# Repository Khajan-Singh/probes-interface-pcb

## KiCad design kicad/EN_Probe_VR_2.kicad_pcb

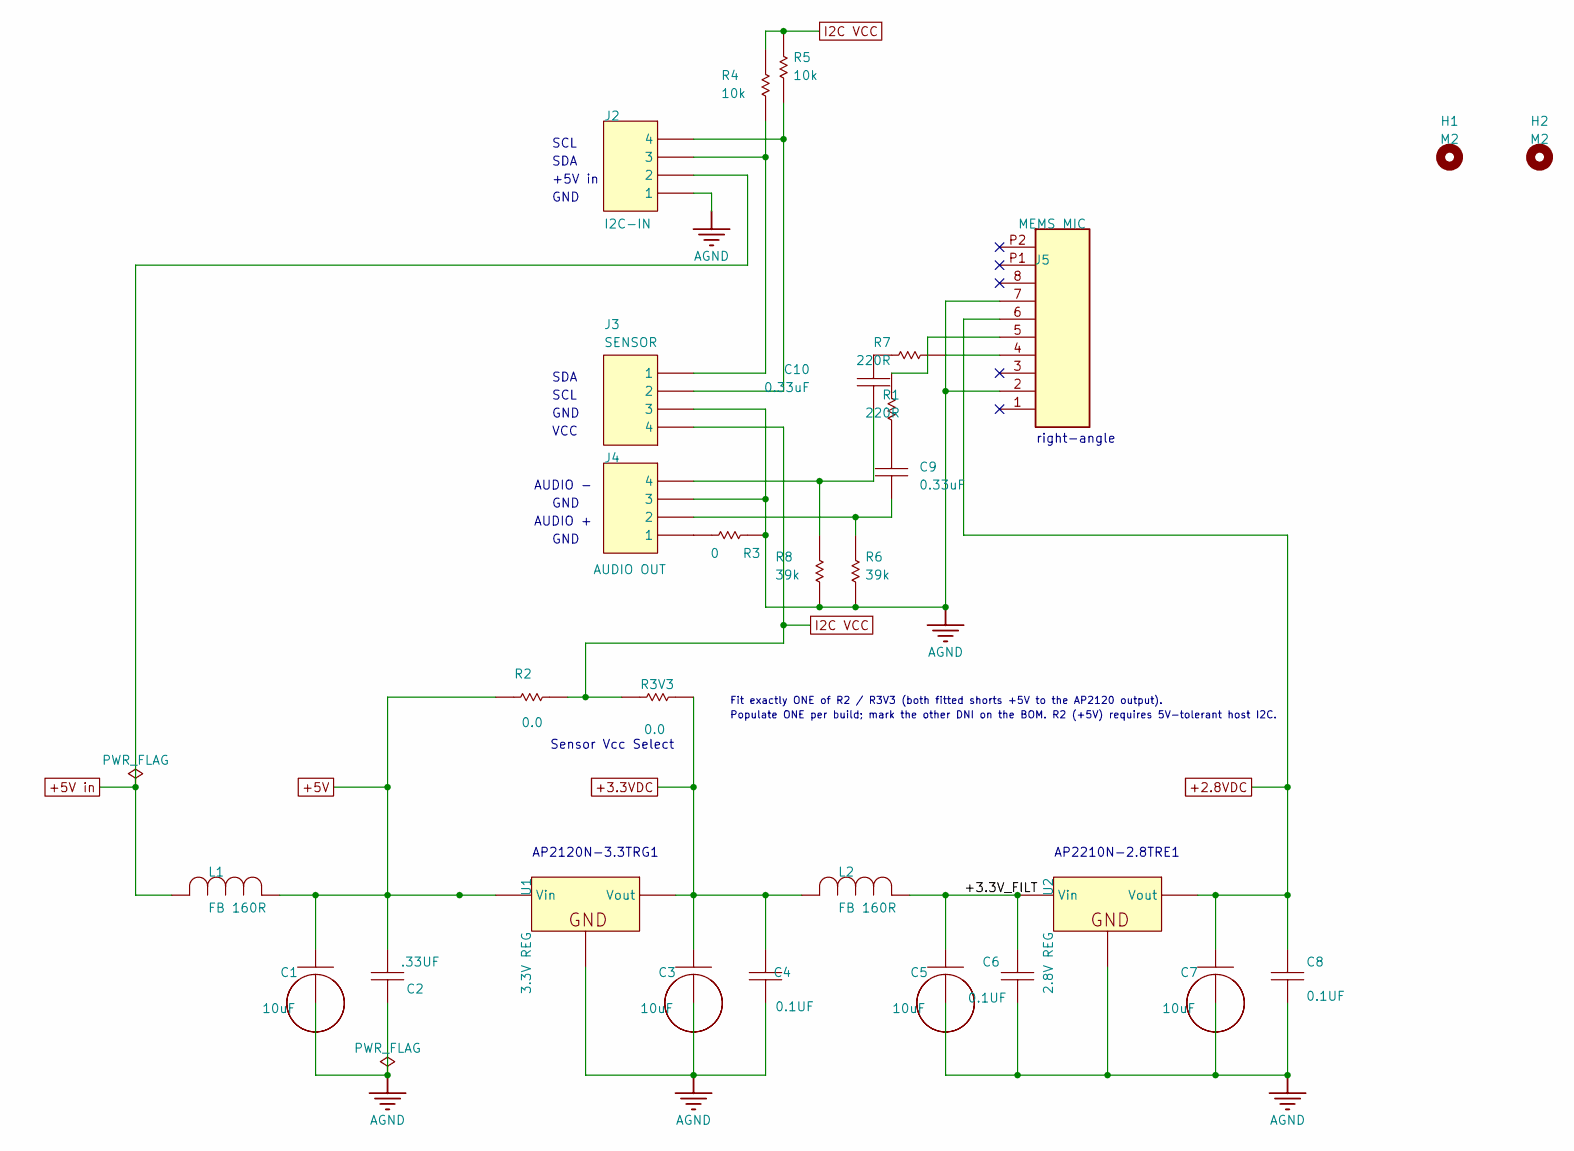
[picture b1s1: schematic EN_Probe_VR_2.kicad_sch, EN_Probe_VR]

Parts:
C1, C3, C5, C7: 10uF; C_0805_2012Metric; MANUFACTURER PART NUMBE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 GRM21BR61E106MA73L
C2: .33UF; C_0805_2012Metric; MANUFACTURER PN CL21B334KAFNNNG
C4, C6, C8: 0.1UF; C_0603_1608Metric; PART FIELD 1 0
C9: 0.33uF; C_0805_2012Metric; MANUFACTURER PN CL21B334KAFNNNG
C10: 0.33uF; C_0805_2012Metric
H1, H2: M2; MountingHole_2.2mm_M2
J2: I2C-IN; PinHeader_1x04_P2.54mm_Vertical; MANUFACTURER PN 640454-4
J3: SENSOR; PinHeader_1x04_P2.54mm_Vertical; MANUFACTURER PN 640454-4
J4: AUDIO OUT; PinHeader_1x04_P2.54mm_Vertical; MANUFACTURER PN 640454-4
J5: MEMS MIC; CON_527450897; MANUFACTURER_PART_NUMBER 527450897
L1, L2: FB 160R; 1206; MANUFACTURER_PART_NUMBER HI1206T161R-10
R1: 220R; R_0805_2012Metric; TOLERANCE_% 5
R2, R3, R3V3: 0R; R_0805_2012Metric; TOLERANCE_% 5
R4, R5: 10k; R_0805_2012Metric
R6, R8: 39k; R_0805_2012Metric
R7: 220R; R_0805_2012Metric
U1: 3.3V REG; SOT23-3; MANUFACTURER PART NUMBE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 AP2120N-3.3TRG1
U2: 2.8V REG; SOT23-3; MANUFACTURER PART NUMBE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 AP2210N-2.8TRE1

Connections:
+2.8VDC: C7.1, C8.2, J5.6, U2.2 (Vout)
+3.3VDC: C3.1, C4.1, L2.2, R3V3.2, U1.2 (Vout)
+5V: C1.1, C2.2, L1.1, R2.2, U1.3 (Vin)
+5V in: J2.2, L1.2
/+3.3V_FILT: C5.1, C6.2, L2.1, U2.3 (Vin)
AGND: C1.2, C2.1, C3.2, C4.2, C5.2, C6.1, C7.2, C8.1, J2.1, J3.3, J4.3, J5.2, J5.7, R3.1, R6.2, R8.2, U1.1 (GND), U2.1 (GND)
I2C VCC: J3.4, R2.1, R3V3.1, R4.1, R5.1
unnamed: C9.1, J4.2, R6.1
unnamed: C9.2, R1.2
unnamed: C10.1, R7.1
unnamed: C10.2, J4.4, R8.1
unnamed: J2.3, J3.1, R4.2
unnamed: J2.4, J3.2, R5.2
unnamed: J4.1, R3.2
unnamed: J5.4, R7.2
unnamed: J5.5, R1.1

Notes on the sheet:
GND
AUDIO +
+5V in
VCC
right-angle
SDA
AP2210N-2.8TRE1
AP2120N-3.3TRG1
SCL
AUDIO -
Fit exactly ONE of R2 / R3V3 (both fitted shorts +5V to the AP2120 output).
Populate ONE per build; mark the other DNI on the BOM. R2 (+5V) requires 5V-tolerant host I2C.
Sensor Vcc Select

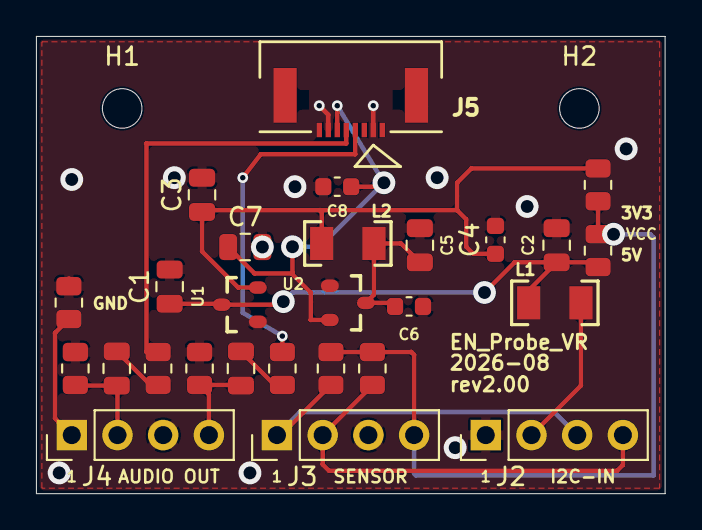
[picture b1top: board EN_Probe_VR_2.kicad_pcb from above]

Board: 2 copper layers, 34.9 x 25.4 mm, 29 parts (0 on the bottom side), 16 nets.

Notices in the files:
parts and their libraries:
COPYRIGHT: Copyright (C) 2018 Accelerated Designs. All rights reserved
COPYRIGHT: Copyright (C) 2023 Ultra Librarian. All rights reserved.
